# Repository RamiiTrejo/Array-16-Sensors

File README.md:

# Array-16-Sensors
Regleta para Robot Seguidor de línea con 16 Sensores QRE1113, siendo multiplexados con dos CD4051, y siendo alimentados a 3,3v, sirviendo para Robots de Carreras, o Carreras Pro

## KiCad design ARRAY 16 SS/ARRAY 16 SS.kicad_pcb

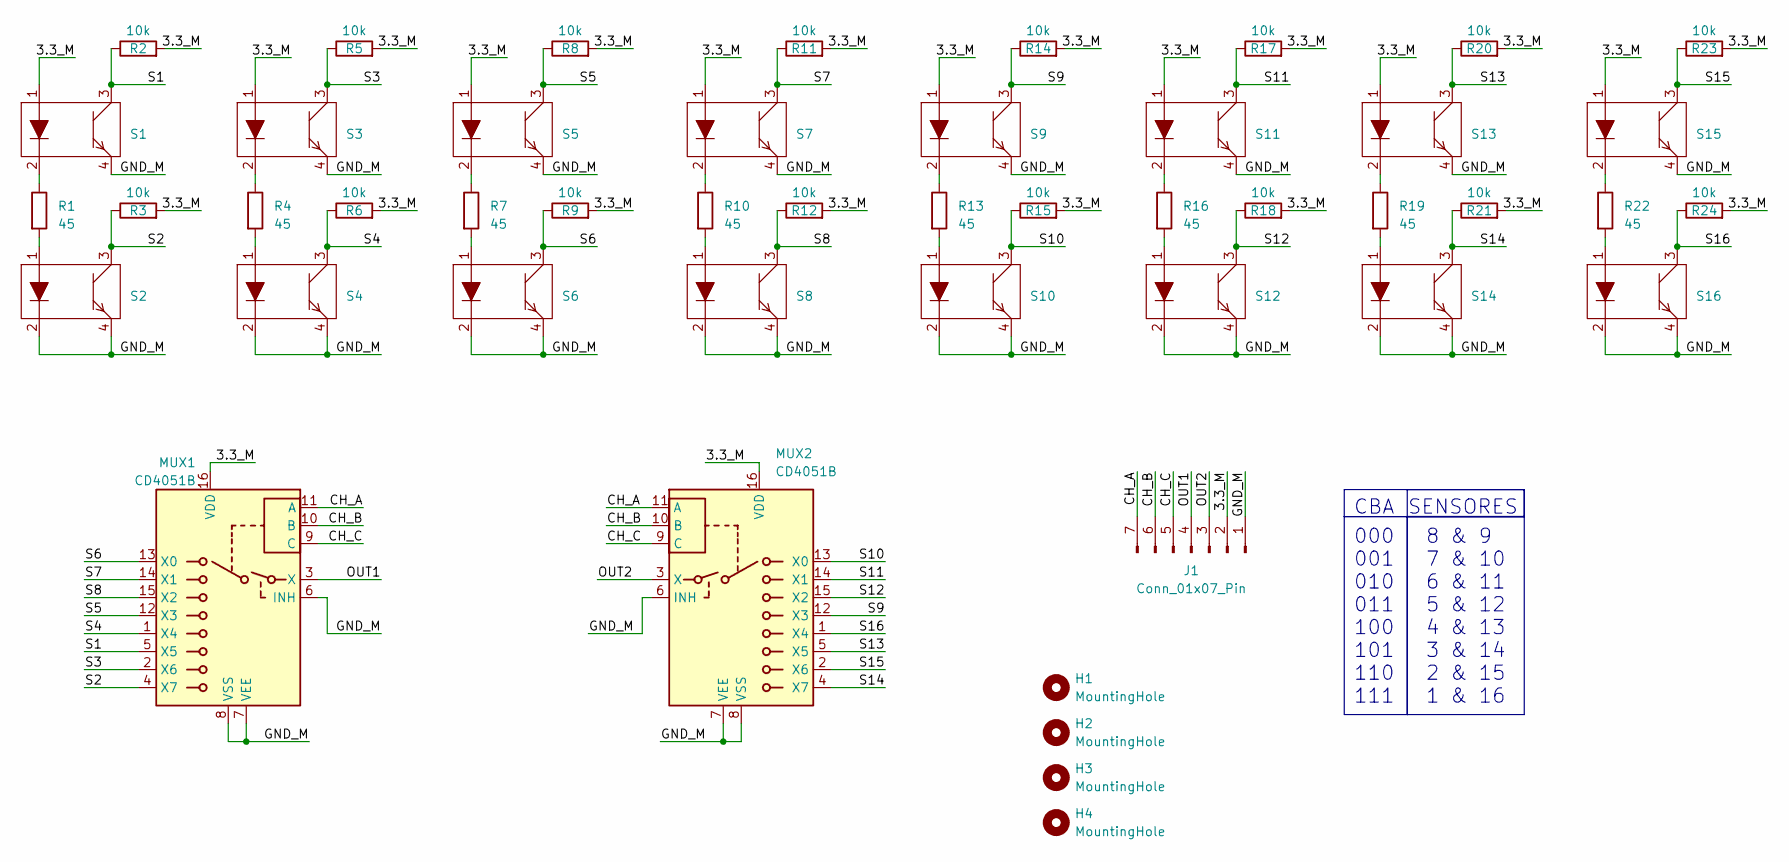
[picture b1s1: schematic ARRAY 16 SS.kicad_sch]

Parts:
H1, H2, H3, H4: MountingHole; MountingHole_3mm
J1: Conn_01x07_Pin; PinHeader_1x07_P2.54mm_Horizontal
MUX1, MUX2: CD4051B; SOIC-16W_5.3x10.2mm_P1.27mm; LCSC Part # C3007951
R1, R4, R7, R10, R13, R16, R19, R22: 45; R_0805_2012Metric_Pad1.20x1.40mm_HandSolder; LCSC Part # C3017827
R2, R3, R5, R6, R8, R9, R11, R12, R14, R15, R17, R18, R20, R21, R23, R24: 10k; R_0805_2012Metric_Pad1.20x1.40mm_HandSolder; LCSC Part # C17414
S1, S2, S3, S4, S5, S6, S7, S8, S9, S10, S11, S12, S13, S14, S15, S16: OnSemi_CASE100CY; LCSC Part # C81632

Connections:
/3.3_M: J1.2, MUX1.16 (VDD), MUX2.16 (VDD), R2.2, R3.2, R5.2, R6.2, R8.2, R9.2, R11.2, R12.2, R14.2, R15.2, R17.2, R18.2, R20.2, R21.2, R23.2, R24.2, S1.1, S3.1, S5.1, S7.1, S9.1, S11.1, S13.1, S15.1
/CH_A: J1.7, MUX1.11 (A), MUX2.11 (A)
/CH_B: J1.6, MUX1.10 (B), MUX2.10 (B)
/CH_C: J1.5, MUX1.9 (C), MUX2.9 (C)
/GND_M: J1.1, MUX1.6 (INH), MUX1.7 (VEE), MUX1.8 (VSS), MUX2.6 (INH), MUX2.7 (VEE), MUX2.8 (VSS), S1.4, S2.2, S2.4, S3.4, S4.2, S4.4, S5.4, S6.2, S6.4, S7.4, S8.2, S8.4, S9.4, S10.2, S10.4, S11.4, S12.2, S12.4, S13.4, S14.2, S14.4, S15.4, S16.2, S16.4
/OUT1: J1.4, MUX1.3 (X)
/OUT2: J1.3, MUX2.3 (X)
/S1: MUX1.5 (X5), R2.1, S1.3
/S2: MUX1.4 (X7), R3.1, S2.3
/S3: MUX1.2 (X6), R5.1, S3.3
/S4: MUX1.1 (X4), R6.1, S4.3
/S5: MUX1.12 (X3), R8.1, S5.3
/S6: MUX1.13 (X0), R9.1, S6.3
/S7: MUX1.14 (X1), R11.1, S7.3
/S8: MUX1.15 (X2), R12.1, S8.3
/S9: MUX2.12 (X3), R14.1, S9.3
/S10: MUX2.13 (X0), R15.1, S10.3
/S11: MUX2.14 (X1), R17.1, S11.3
/S12: MUX2.15 (X2), R18.1, S12.3
/S13: MUX2.5 (X5), R20.1, S13.3
/S14: MUX2.4 (X7), R21.1, S14.3
/S15: MUX2.2 (X6), R23.1, S15.3
/S16: MUX2.1 (X4), R24.1, S16.3
unnamed: R1.1, S1.2
unnamed: R1.2, S2.1
unnamed: R4.1, S3.2
unnamed: R4.2, S4.1
unnamed: R7.1, S5.2
unnamed: R7.2, S6.1
unnamed: R10.1, S7.2
unnamed: R10.2, S8.1
unnamed: R13.1, S9.2
unnamed: R13.2, S10.1
unnamed: R16.1, S11.2
unnamed: R16.2, S12.1
unnamed: R19.1, S13.2
unnamed: R19.2, S14.1
unnamed: R22.1, S15.2
unnamed: R22.2, S16.1

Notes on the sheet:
SENSORES
8 & 9 7 & 10 6 & 11 5 & 12 4 & 13 3 & 14 2 & 15 1 & 16
CBA
000 001 010 011 100 101 110 111

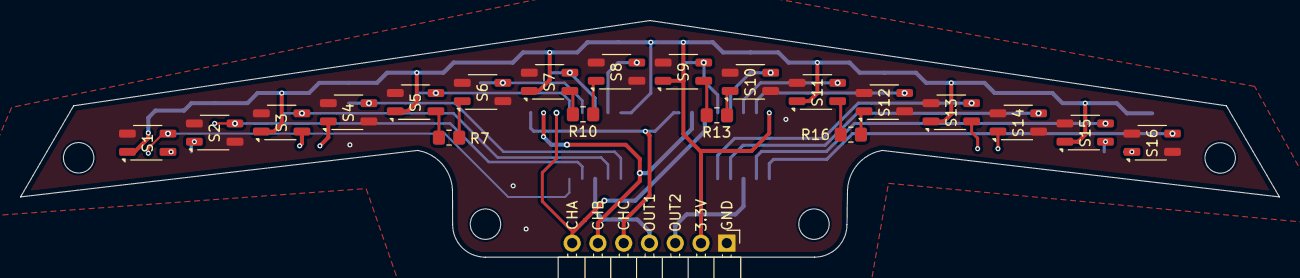
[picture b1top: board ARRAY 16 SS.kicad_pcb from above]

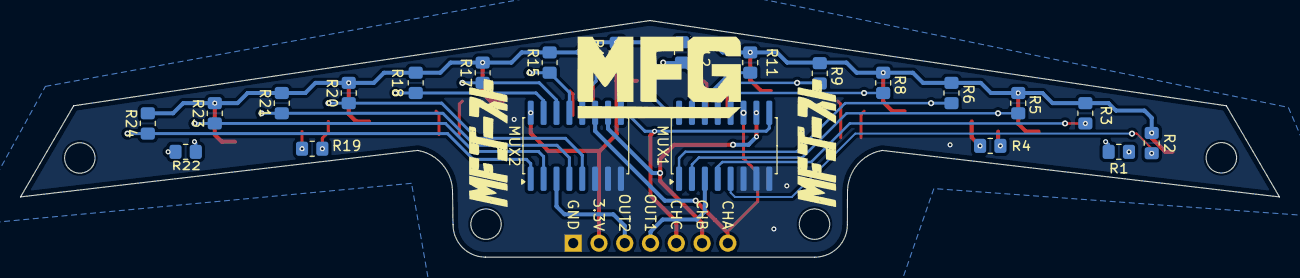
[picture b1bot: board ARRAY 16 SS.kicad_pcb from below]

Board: 2 copper layers, 124.1 x 23.3 mm, 47 parts (22 on the bottom side), 39 nets.
